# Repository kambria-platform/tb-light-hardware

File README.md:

# tb-light-hardware	 
Eagle board design and BOM for LED strip controller.

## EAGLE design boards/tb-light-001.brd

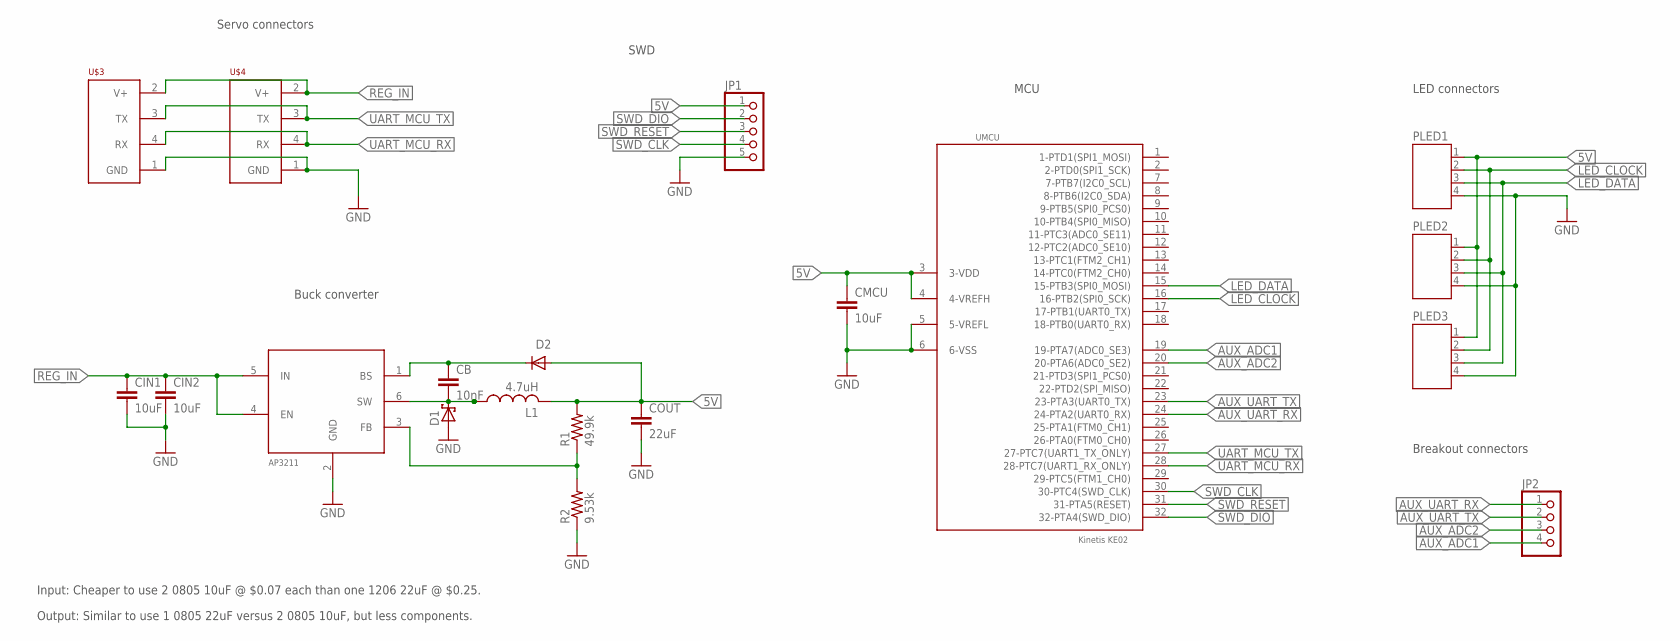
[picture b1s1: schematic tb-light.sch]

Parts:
CB: 10nF; C0805; DIGIKEY# 1276-1015-1-ND
CIN1, CIN2: 10uF; C0805; DIGIKEY# 490-5523-1-ND
CMCU: 10uF; C0805; DIGIKEY# 490-5523-1-ND
COUT: 22uF; C0805; DIGIKEY# 490-10511-1-ND
D1: SCHOTTKY; SOD-123FL; DIGIKEY# DB2X41500LCT-ND
D2: SMALL-SIGNALSOD-123; SOD-123; DIGIKEY# 1N4148W-FDICT-ND
JP1: PINHD-1X5; 1X05; DIGIKEY# MANUAL_PLACE
JP2: PINHD-1X4; 1X04; DIGIKEY# DNP
L1: 4.7uH; L_NR6028; DIGIKEY# 587-2100-1-ND
PLED1, PLED2, PLED3: JST-PH4; DIGIKEY# 455-1706-ND
R1: 49.9k; R0805; DIGIKEY# 311-49.9KCRCT-ND
R2: 9.53k; R0805; DIGIKEY# 311-9.53KCRCT-ND
U$3, U$4: SERVO-CONNVERT; TE-AMP-4PIN; DIGIKEY# A98779-ND
UMCU: KE02; TQFP32-08; DIGIKEY# MKE02Z32VLC4-ND
UREG: AP3211; SOT23-6; DIGIKEY# AP3211KTR-G1DICT-ND

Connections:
5V: CMCU.1, COUT.1, D2.A, JP1.1, L1.P$2 (2), PLED1.1, PLED2.1, PLED3.1, R1.2, UMCU.3 (3-VDD), UMCU.4 (4-VREFH)
AUX_ADC1: JP2.4, UMCU.19 (19-PTA7(ADC0_SE3))
AUX_ADC2: JP2.3, UMCU.20 (20-PTA6(ADC0_SE2))
AUX_UART_RX: JP2.1, UMCU.24 (24-PTA2(UART0_RX))
AUX_UART_TX: JP2.2, UMCU.23 (23-PTA3(UART0_TX))
GND: CIN1.2, CIN2.2, CMCU.2, COUT.2, D1.A, JP1.5, PLED1.4, PLED2.4, PLED3.4, R2.1, U$3.1 (GND), U$4.1 (GND), UMCU.5 (5-VREFL), UMCU.6 (6-VSS), UREG.2 (GND)
LED_CLOCK: PLED1.2, PLED2.2, PLED3.2, UMCU.16 (16-PTB2(SPI0_SCK))
LED_DATA: PLED1.3, PLED2.3, PLED3.3, UMCU.15 (15-PTB3(SPI0_MOSI))
unnamed: R1.1, R2.2, UREG.3 (FB)
unnamed: CB.2, D1.C, L1.P$1 (1), UREG.6 (SW)
unnamed: CB.1, D2.C, UREG.1 (BS)
REG_IN: CIN1.1, CIN2.1, U$3.2 (V+), U$4.2 (V+), UREG.4 (EN), UREG.5 (IN)
SWD_CLK: JP1.4, UMCU.30 (30-PTC4(SWD_CLK))
SWD_DIO: JP1.2, UMCU.32 (32-PTA4(SWD_DIO))
SWD_RESET: JP1.3, UMCU.31 (31-PTA5(RESET))
UART_MCU_RX: U$3.4 (RX), U$4.4 (RX), UMCU.28 (28-PTC7(UART1_RX_ONLY))
UART_MCU_TX: U$3.3 (TX), U$4.3 (TX), UMCU.27 (27-PTC7(UART1_TX_ONLY))

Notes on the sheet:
Input: Cheaper to use 2 0805 10uF @ $0.07 each than one 1206 22uF @ $0.25.
Output: Similar to use 1 0805 22uF versus 2 0805 10uF, but less components.
Servo connectors
Buck converter
MCU
LED connectors
Breakout connectors
SWD

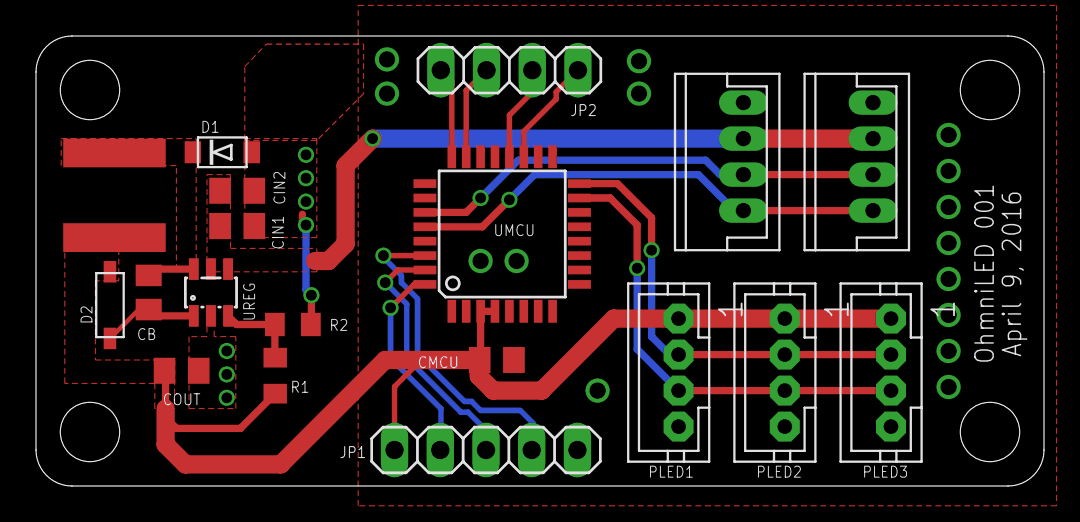
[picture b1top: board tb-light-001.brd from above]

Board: 2 copper layers, 56.0 x 25.0 mm, 20 parts (1 on the bottom side), 17 nets.

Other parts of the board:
U$1: LOGO-HORIZ-SMALL

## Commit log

2018-03-13 typo in semantic type
2018-03-13 rename semantic_type
2018-03-14 move files
2018-05-07 remove .ds_store
2018-05-08 updated bom with links
2018-05-08 removed ds_store
2018-05-08 updated kdna for BOM display fields
2018-05-08 fixed bom with null links
2018-05-08 link reference for field hearders
